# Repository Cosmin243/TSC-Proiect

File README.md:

# OpenBook – Cititor de Cărți Electronice Open-Source

OpenBook este un dispozitiv de tip e-book reader cu sursă deschisă, proiectat să fie accesibil și eficient. Creat în cadrul inițiativei TSC, dispozitivul este construit în jurul microcontrolerului ESP32-C6, oferind funcții avansate de afișare, conectivitate și consum energetic redus. Designul său este pregătit pentru producția de serie.

# Diagrama

# [BOM] - Bill of Materials

| Componentă             | Descriere                            | Link |
|------------------------|--------------------------------------|------|
| ESP32-C6-WROOM-1-N8    | Wi-Fi, BLE, Zigbee SoC Module        | [Link](https://www.snapeda.com/parts/ESP32-C6-WROOM-1-N8/Espressif+Systems/view-part/) |
| BME680                 | Environmental Sensor                 | [Link](https://www.snapeda.com/parts/BME680/Bosch/view-part/?welcome=home) |
| MCP73831               | Li-Po Battery Charging Controller    | [Link](https://www.digikey.com/en/products/detail/microchip-technology/MCP73831T-2ACI-OT/1874108) |
| DS3231SN               | Real-Time Clock                      | [Link](https://www.snapeda.com/parts/DS3231SN%23/Analog+Devices/view-part/) |
| MAX17048G+T10          | Battery Fuel Gauge                   | [Link](https://www.digikey.com/en/products/detail/analog-devices-inc-maxim-integrated/MAX17048G-T10/9357632) |
| W25Q512JVEIQ           | 512Mb Flash Memory                   | [Link](https://www.snapeda.com/parts/W25Q512JVEIQ/Winbond/view-part/) |
| USB4110-GF-A           | USB Type-C Connector                 | [Link](https://www.digikey.com/en/products/detail/amphenol-commercial-products/USB4110-GF-A/6039334) |
| 112A-TAAR-R03          | Micro SD Card Connector              | [Link](https://store.comet.bg/en/Catalogue/Product/43497/) |
| XC6220A331MR-G         | LDO Voltage Regulator                | [Link](https://www.lcsc.com/product-detail/LDO-Voltage-Regulators_Torex-Semicon-XC6220A331MR-G_C35154.html) |
| SI1308EDL-T1-GE3       | N-Channel MOSFET                     | [Link](https://www.digikey.com/en/products/detail/vishay-siliconix/SI1308EDL-T1-GE3/770967) |
| DMG2305UX-7            | P-Channel MOSFET                     | [Link](https://www.digikey.com/en/products/detail/diodes-incorporated/DMG2305UX-7/2713557) |
| USBLC6-2SC6Y           | USB ESD Protection                   | [Link](https://www.digikey.com/en/products/detail/stmicroelectronics/USBLC6-2SC6Y/458756) |
| MBR0530                | Schottky Diode                       | [Link](https://www.digikey.com/en/products/detail/onsemi/MBR0530T1G/965411) |
| CPH3225                | 11mF Supercapacitor                  | [Link](https://www.snapeda.com/parts/CPH3225A/Seiko+Instruments/view-part/) |
| CC0402                 | Capacitor                            | [Link](https://componentsearchengine.com/part-view/CC0402MRX5R5BB106/YAGEO) |
| RR0402                 | Resistor                             | [Link](https://www.snapeda.com/parts/RC0402FR-07226RL/Yageo/view-part/) |

Dispozitivul suportă mai multe surse de alimentare:

- **USB-C**: Alimentare și comunicare prin conectorul `USB4110-GF-A`, cu protecție ESD (`USBLC6-2SC6Y`)
- **Baterie Li-Po**: Încărcată prin controlerul `MCP73831`, cu indicator de stare LED
- **Backup cu supercondensator**: `CPH3225A` menține alimentarea ceasului RTC în caz de pierdere de curent

**Calea de alimentare include:**

- `XC6220A331MR-G` – LDO care furnizează 3.3V stabil pentru sistem
- `MAX17048G+T10` – Fuel gauge pentru monitorizarea capacității bateriei
- `DMG2305UX-7` – MOSFET P-Channel pentru selecția automată a sursei de alimentare
- `MBR0530` – Diodă Schottky pentru protecție la tensiuni inverse

---

## Procesare & Memorie

- `ESP32-C6-WROOM-1-N8` – Microcontroller principal cu suport pentru Wi-Fi 6, Bluetooth 5 și Zigbee 3.0
- `W25Q512JVEIQ` – Memorie Flash SPI externă de 512Mb pentru stocare extinsă
- **Slot microSD** – Permite extinderea stocării pentru datele utilizatorului

---

## Senzori & Ceas

- `BME680` – Senzor ambiental I²C ce măsoară:
  - Temperatură: -40°C până la +85°C  
  - Umiditate: 0–100% RH  
  - Presiune: 300–1100 hPa  
  - Calitatea aerului (rezistență la gaze)
- `DS3231SN` – Ceas în timp real I²C cu compensare termică, foarte precis

---

## Conectivitate & Interfețe

- **USB-C** – Pentru alimentare, încărcare și comunicare de date
- **Qwiic / STEMMA QT** – Conector I²C rapid pentru extensii externe (senzori, periferice)
- **I²C & SPI** – Utilizate pentru senzori și memorie
- **Mod Deep Sleep** – ESP32 intră în standby (~20 µA) pentru autonomie crescută

---

## Interfață Utilizator

- **Buton Reset** – Repornește dispozitivul
- **Buton Boot** – Permite accesul în modul bootloader pentru programare
- **Buton Change** – Poate fi folosit pentru interacțiuni cu conținutul afișat

# 🧷 Pini ESP32-C6

| GPIO  | Componentă       |
|-------|------------------|
| IO9   | Boot Button      |
| IO2   | SD Card          |
| IO4   | SD Card          |
| IO21  | I2C Shared       |
| IO6   | SPI Shared       |
| IO22  | I2C Shared       |
| IO7   | SPI Shared       |
| IO0   | RTC              |
| IO13  | USB Interface    |
| IO19  | MAX17048         |
| IO11  | NOR Flash        |
| IO12  | USB Interface    |
| IO1   | RTC              |
| IO8   | GPIO             |
| IO15  | Buton Change     |
| IO18  | RTC              |
| IO17  | UART             |
| IO16  | UART             |
| EN    | Buton Reset      |

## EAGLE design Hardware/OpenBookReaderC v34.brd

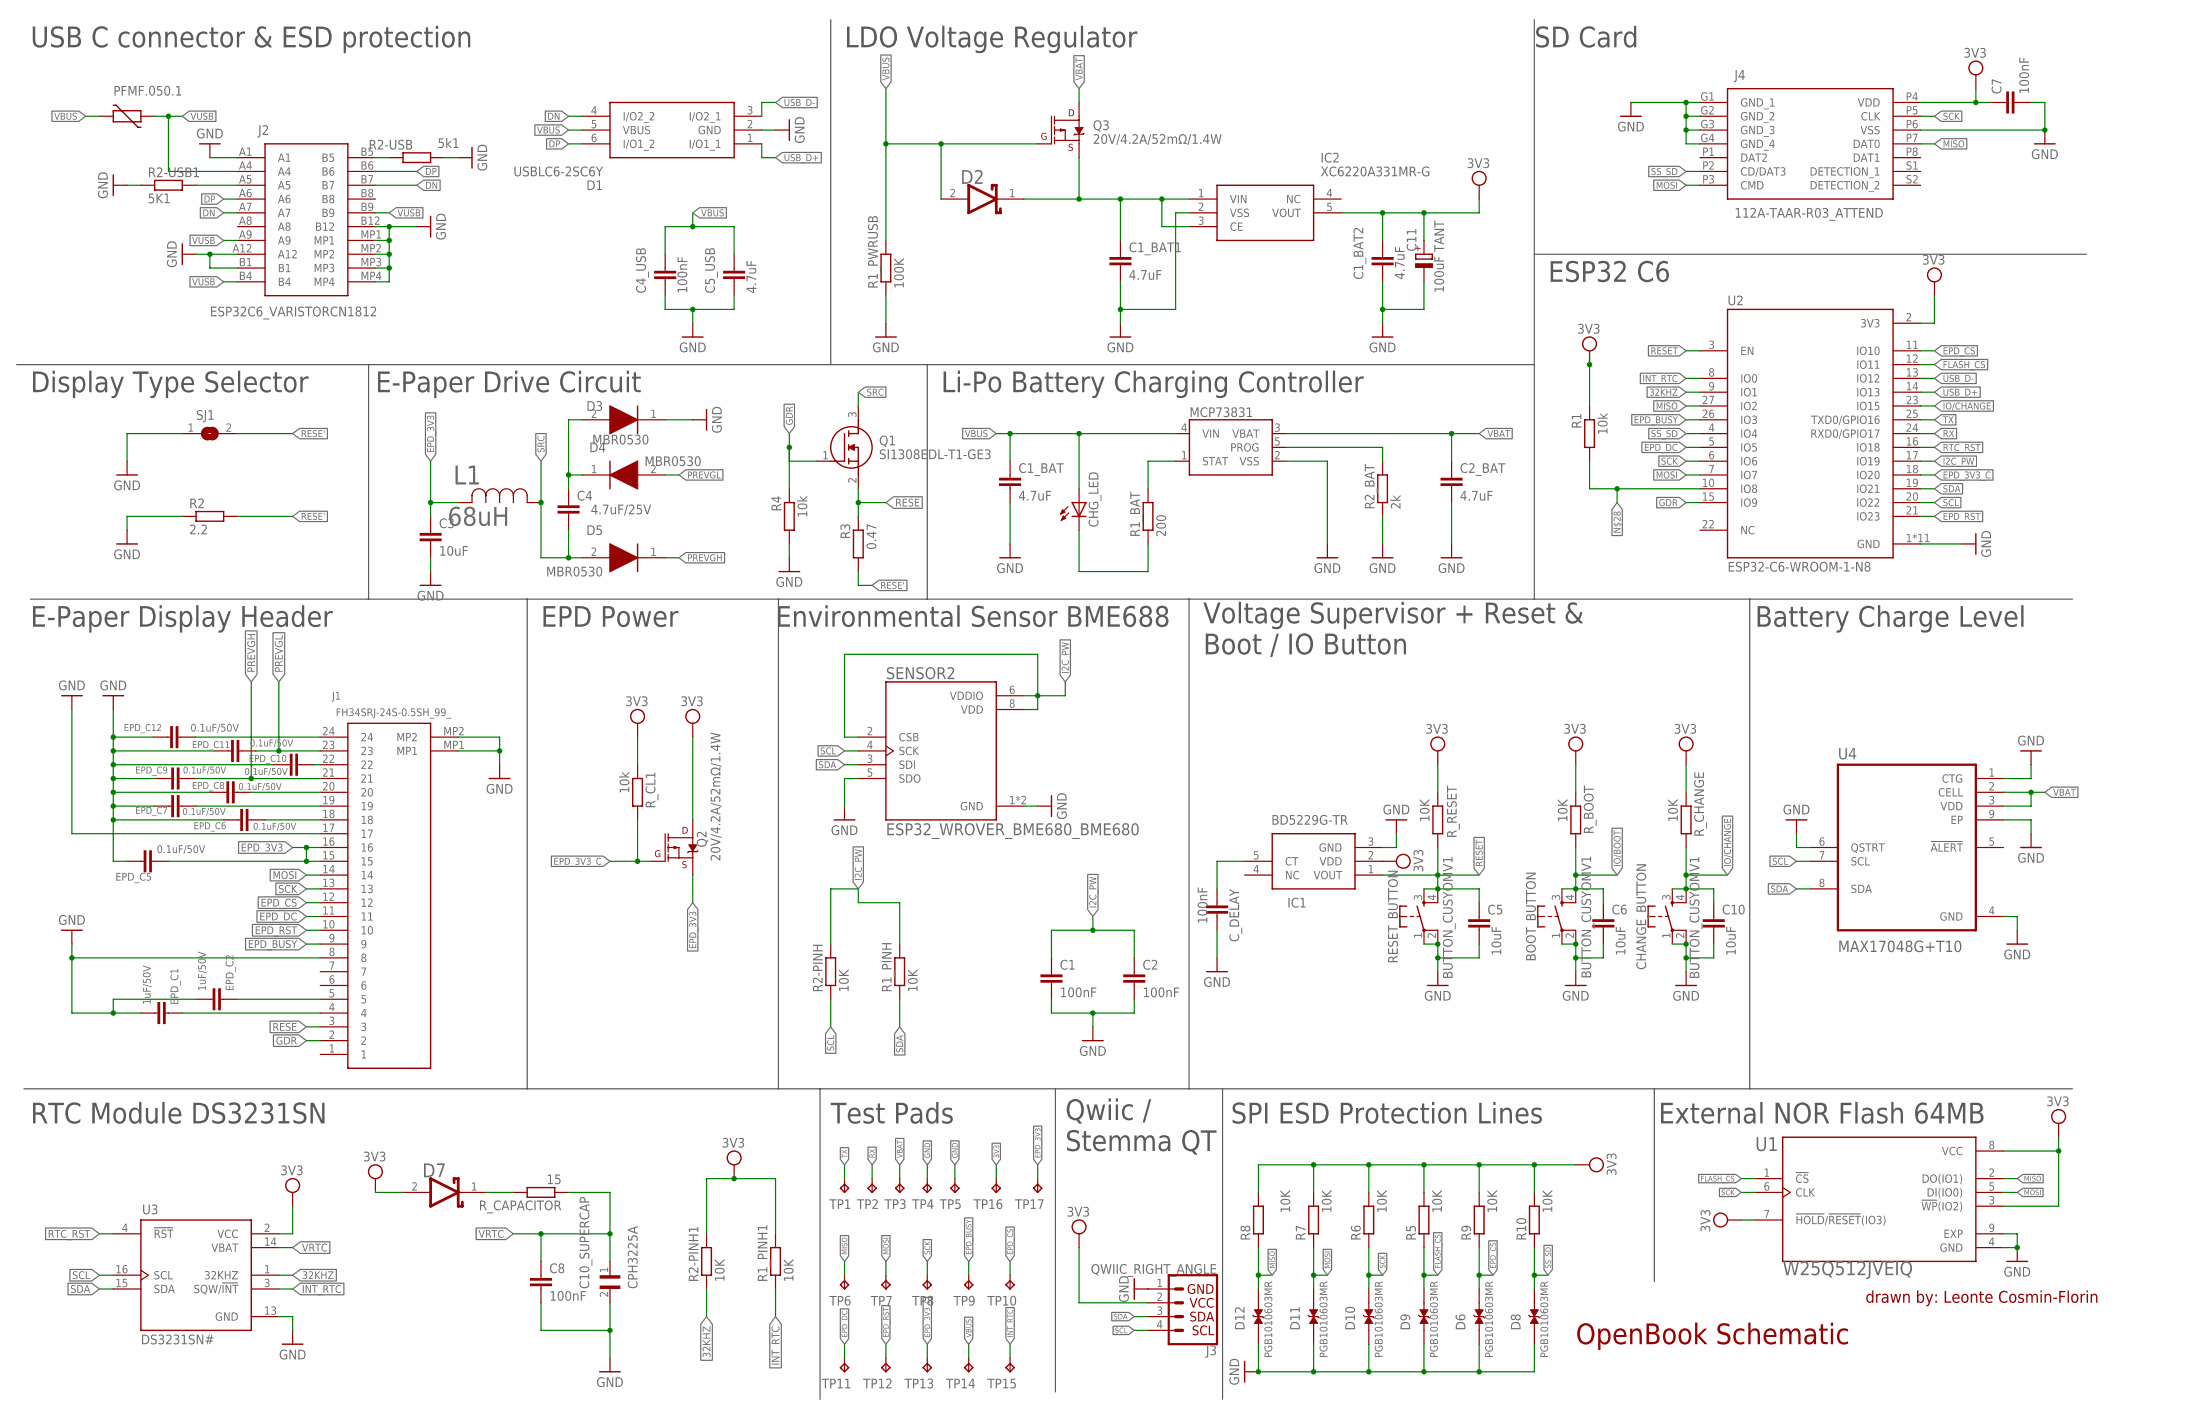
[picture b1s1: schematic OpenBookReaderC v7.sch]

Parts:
BOOT_BUTTON: BUTTON_CUSYOMV1; MYBUTTON
C1, C2, C4_USB, C7, C8: 100nF; ESP32_WROVER_EAGLE-LTSPICE_C0402
C1_BAT, C1_BAT1, C1_BAT2, C2_BAT, C5_USB: 4.7uF; ESP32_WROVER_EAGLE-LTSPICE_C0402
C3, C5, C6, C10: 10uF; ESP32_WROVER_EAGLE-LTSPICE_C0402
C4: 4.7uF/25V; ESP32_WROVER_EAGLE-LTSPICE_C0402
C10_SUPERCAP: CPH3225A; CAPCP3225X100N
C11: 100uF TANT; RCL_CT3528
CHANGE_BUTTON: BUTTON_CUSYOMV1; MYBUTTON
CHG_LED: ADAFRUIT_LEDCHIP-LED0603; ADAFRUIT_CHIP-LED0603
C_DELAY: 100nF; ESP32_WROVER_EAGLE-LTSPICE_C0402
D1: USBLC6-2SC6Y; SOT95P280X145-6N
D2, D7: ESP32_WROVER_AVX---SD0805S020S1R0_AVX_SD0805S020S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; ESP32_WROVER_AVX---SD0805S020S1R0_AVX_SD0805S020S1R0_0
D3, D4, D5: MBR0530; SOD3716X135N
D6, D8, D9, D10, D11, D12: PGB1010603MR; DIOC1608X36N
EPD_C1, EPD_C2: 1uF/50V; ESP32_WROVER_EAGLE-LTSPICE_C0402
EPD_C5, EPD_C6, EPD_C7, EPD_C8, EPD_C9, EPD_C10, EPD_C11, EPD_C12: 0.1uF/50V; ESP32_WROVER_EAGLE-LTSPICE_C0402
IC1: BD5229G-TR; SOT95P280X125-5N
IC2: XC6220A331MR-G; SOT95P280X120-5N
J1: FH34SRJ-24S-0.5SH_99_; FH34SRJ24S05SH99
J2: SAMACSYS_PARTS_USB4110-GF-A; SAMACSYS_PARTS_USB4110GFA
J3: QWIIC_RIGHT_ANGLE; JST04_1MM_RA
J4: 112A-TAAR-R03_ATTEND; 112ATAARR03ATTEND
L1: 68uH; IND_4828-WE-TPC_WRE
MCP73831: ESP32_WROVER_SPARKFUN-IC-POWER_MCP73831; ESP32_WROVER_SPARKFUN-IC-POWER_SOT23-5
PFMF.050.1: ESP32C6_VARISTORCN1812; ESP32C6_VARISTOR_CT/CN1812
Q1: SI1308EDL-T1-GE3; SOT65P210X110-3N
Q2, Q3: 20V/4.2A/52mΩ/1.4W; ESP32_WROVER_SPARKFUN-DISCRETESEMI_SOT23-3
R1, R4: 10k; ESP32_WROVER_EAGLE-LTSPICE_R0402
R1_BAT: 200; ESP32_WROVER_EAGLE-LTSPICE_R0402
R1_PINH, R1_PINH1, R2-PINH, R2-PINH1, R5, R6, R7, R8, R9, R10: 10K; ESP32_WROVER_EAGLE-LTSPICE_R0402
R1_PWRUSB: 100K; ESP32_WROVER_EAGLE-LTSPICE_R0402
R2: 2.2; ESP32_WROVER_EAGLE-LTSPICE_R0402
R2-USB: 5k1; ESP32_WROVER_EAGLE-LTSPICE_R0402
R2-USB1: 5K1; ESP32_WROVER_EAGLE-LTSPICE_R0402
R2_BAT: 2k; ESP32_WROVER_EAGLE-LTSPICE_R0402
R3: 0.47; ESP32_WROVER_EAGLE-LTSPICE_R0402
RESET_BUTTON: BUTTON_CUSYOMV1; MYBUTTON
R_BOOT: 10K; ESP32_WROVER_EAGLE-LTSPICE_R0402
R_CAPACITOR: 15; ESP32_WROVER_EAGLE-LTSPICE_R0402
R_CHANGE: 10K; ESP32_WROVER_EAGLE-LTSPICE_R0402
R_CL1: 10k; ESP32_WROVER_EAGLE-LTSPICE_R0402
R_RESET: 10K; ESP32_WROVER_EAGLE-LTSPICE_R0402
SENSOR2: ESP32_WROVER_BME680_BME680; ESP32_WROVER_BME680_PSON80P300X300X100-8N
SJ1: SJ
TP1, TP2, TP3, TP4, TP5, TP6, TP7, TP8, TP9, TP10, TP11, TP12, TP13, TP14, TP15, TP16, TP17: TPTP20R; TP20R
U1: W25Q512JVEIQ; SON127P600X800X80-9N
U2: ESP32-C6-WROOM-1-N8; XCVR_ESP32-C6-WROOM-1-N8
U3: DS3231SN#; SOIC127P1032X265-16N
U4: MAX17048G+T10; SON50P200X200X80-9N

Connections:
3V3: C1_BAT2.1, C7.1, C11.+, D7.2 (ANODE), IC1.2 (VDD), IC2.5 (VOUT), J3.2, J4.P4 (VDD), Q2.3 (D), R1.1, R1_PINH1.2, R2-PINH1.2, R5.2, R6.2, R7.2, R8.2, R9.2, R10.2, R_BOOT.1, R_CHANGE.1, R_CL1.1, R_RESET.1, TP16.TP, U1.3 (!WP!(IO2)), U1.7 (!HOLD!/!RESET!(IO3)), U1.8 (VCC), U2.2 (3V3), U3.2 (VCC)
32KHZ: R2-PINH1.1, U2.9 (IO1), U3.1 (32KHZ)
DN: D1.4 (I/O2_2), J2.A7, J2.B7
DP: D1.6 (I/O1_2), J2.A6, J2.B6
EPD_3V3: C3.1, EPD_C5.1, J1.15, J1.16, L1.2, Q2.2 (S), TP17.TP
EPD_3V3_C: Q2.1 (G), R_CL1.2, TP13.TP, U2.18 (IO20)
EPD_BUSY: J1.9, TP9.TP, U2.26 (IO3)
EPD_CS: D6.2, J1.12, R9.1, TP10.TP, U2.11 (IO10)
EPD_DC: J1.11, TP11.TP, U2.5 (IO5)
EPD_RST: J1.10, TP12.TP, U2.21 (IO23)
FLASH_CS: D9.2, R5.1, U1.1 (!CS), U2.12 (IO11)
GDR: J1.2, Q1.1 (G), R4.1, U2.15 (IO9)
GND: BOOT_BUTTON.1, BOOT_BUTTON.2, C1.2, C1_BAT.2, C1_BAT1.2, C1_BAT2.2, C2.2, C2_BAT.2, C3.2, C4_USB.2, C5.2, C5_USB.2, C6.2, C7.2, C8.2, C10.2, C10_SUPERCAP.2, C11.-, CHANGE_BUTTON.1, CHANGE_BUTTON.2, C_DELAY.2, D1.2 (GND), D3.1 (K), D6.1, D8.1, D9.1, D10.1, D11.1, D12.1, EPD_C1.2, EPD_C2.2, EPD_C5.2, EPD_C6.2, EPD_C7.2, EPD_C8.2, EPD_C9.2, EPD_C10.2, EPD_C11.2, EPD_C12.2, IC1.3 (GND), IC2.2 (VSS), J1.8, J1.17, J1.MP1, J1.MP2, J2.A1, J2.A12, J2.B1, J2.B12, J2.MP1, J2.MP2, J2.MP3, J2.MP4, J3.1, J4.G1 (GND_1), J4.G2 (GND_2), J4.G3 (GND_3), J4.G4 (GND_4), J4.P6 (VSS), MCP73831.2 (VSS), R1_PWRUSB.1, R2.1, R2-USB.2, R2-USB1.1, R2_BAT.1, R4.2, RESET_BUTTON.1, RESET_BUTTON.2, SENSOR2.1 (GND), SENSOR2.5 (SDO), SENSOR2.7 (GND), SJ1.1, TP4.TP, TP5.TP, U1.4 (GND), U1.9 (EXP), U2.1 (GND), U2.28 (GND), U2.29_1 (GND), U2.29_2 (GND), U2.29_3 (GND), U2.29_4 (GND), U2.29_5 (GND), U2.29_6 (GND), U2.29_7 (GND), U2.29_8 (GND), U2.29_9 (GND), U3.13 (GND), U4.1 (CTG), U4.4 (GND), U4.6 (QSTRT), U4.9 (EP)
I2C_PW: C1.1, C2.1, R1_PINH.2, R2-PINH.2, SENSOR2.2 (CSB), SENSOR2.6 (VDDIO), SENSOR2.8 (VDD), U2.17 (IO19)
INT_RTC: R1_PINH1.1, TP15.TP, U2.8 (IO0), U3.3 (SQW/!INT)
IO/BOOT: BOOT_BUTTON.3, BOOT_BUTTON.4, C6.1, R_BOOT.2
IO/CHANGE: C10.1, CHANGE_BUTTON.3, CHANGE_BUTTON.4, R_CHANGE.2, U2.23 (IO15)
MISO: D12.2, J4.P7 (DAT0), R8.1, TP6.TP, U1.2 (DO(IO1)), U2.27 (IO2)
MOSI: D11.2, J1.14, J4.P3 (CMD), R7.1, TP7.TP, U1.5 (DI(IO0)), U2.7 (IO7)
unnamed: EPD_C1.1, J1.4
unnamed: EPD_C2.1, J1.5
unnamed: D7.1 (CATHODE), R_CAPACITOR.2
unnamed: EPD_C6.1, J1.18
unnamed: EPD_C7.1, J1.19
unnamed: EPD_C8.1, J1.20
unnamed: C_DELAY.1, IC1.5 (CT)
unnamed: EPD_C10.1, J1.22
unnamed: C4.1, D3.2 (A), D4.1 (K)
unnamed: EPD_C12.1, J1.24
unnamed: J2.B5, R2-USB.1
unnamed: MCP73831.1 (STAT), R1_BAT.2
unnamed: CHG_LED.C, R1_BAT.1
unnamed: MCP73831.5 (PROG), R2_BAT.2
unnamed: C1_BAT1.1, D2.1 (CATHODE), IC2.1 (VIN), IC2.3 (CE), Q3.2 (S)
unnamed: J2.A5, R2-USB1.2
unnamed: R1.2, U2.10 (IO8)
PREVGH: D5.1 (K), EPD_C9.1, J1.21
PREVGL: D4.2 (A), EPD_C11.1, J1.23
RESE: J1.3, Q1.2 (S), R3.1
RESE': R2.2, R3.2, SJ1.2
RESET: C5.1, IC1.1 (VOUT), RESET_BUTTON.3, RESET_BUTTON.4, R_RESET.2, U2.3 (EN)
RTC_RST: U2.16 (IO18), U3.4 (!RST)
RX: TP2.TP, U2.24 (RXD0/GPIO17)
SCK: D10.2, J1.13, J4.P5 (CLK), R6.1, TP8.TP, U1.6 (CLK), U2.6 (IO6)
SCL: J3.4, R2-PINH.1, SENSOR2.4 (SCK), U2.20 (IO22), U3.16 (SCL), U4.7 (SCL)
SDA: J3.3, R1_PINH.1, SENSOR2.3 (SDI), U2.19 (IO21), U3.15 (SDA), U4.8 (SDA)
SRC: C4.2, D5.2 (A), L1.1, Q1.3 (D)
SS_SD: D8.2, J4.P2 (CD/DAT3), R10.1, U2.4 (IO4)
TX: TP1.TP, U2.25 (TXD0/GPIO16)
USB_D+: D1.1 (I/O1_1), U2.14 (IO13)
USB_D-: D1.3 (I/O2_1), U2.13 (IO12)
VBAT: C2_BAT.1, MCP73831.3 (VBAT), Q3.3 (D), TP3.TP, U4.2 (CELL), U4.3 (VDD)
VBUS: C1_BAT.1, C4_USB.1, C5_USB.1, CHG_LED.A, D1.5 (VBUS), D2.2 (ANODE), MCP73831.4 (VIN), PFMF.050.1.2, Q3.1 (G), R1_PWRUSB.2, TP14.TP
VRTC: C8.1, C10_SUPERCAP.1, R_CAPACITOR.1, U3.14 (VBAT)
VUSB: J2.A4, J2.A9, J2.B4, J2.B9, PFMF.050.1.1

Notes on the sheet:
E-Paper Display Header
RTC Module DS3231SN
Test Pads
Qwiic / Stemma QT
SPI ESD Protection Lines
External NOR Flash 64MB
Battery Charge Level
Voltage Supervisor + Reset & Boot / IO Button
Environmental Sensor BME688
EPD Power
Display Type Selector
E-Paper Drive Circuit
Li-Po Battery Charging Controller
ESP32 C6
SD Card
LDO Voltage Regulator
USB C connector & ESD protection
OpenBook Schematic
drawn by: Leonte Cosmin-Florin

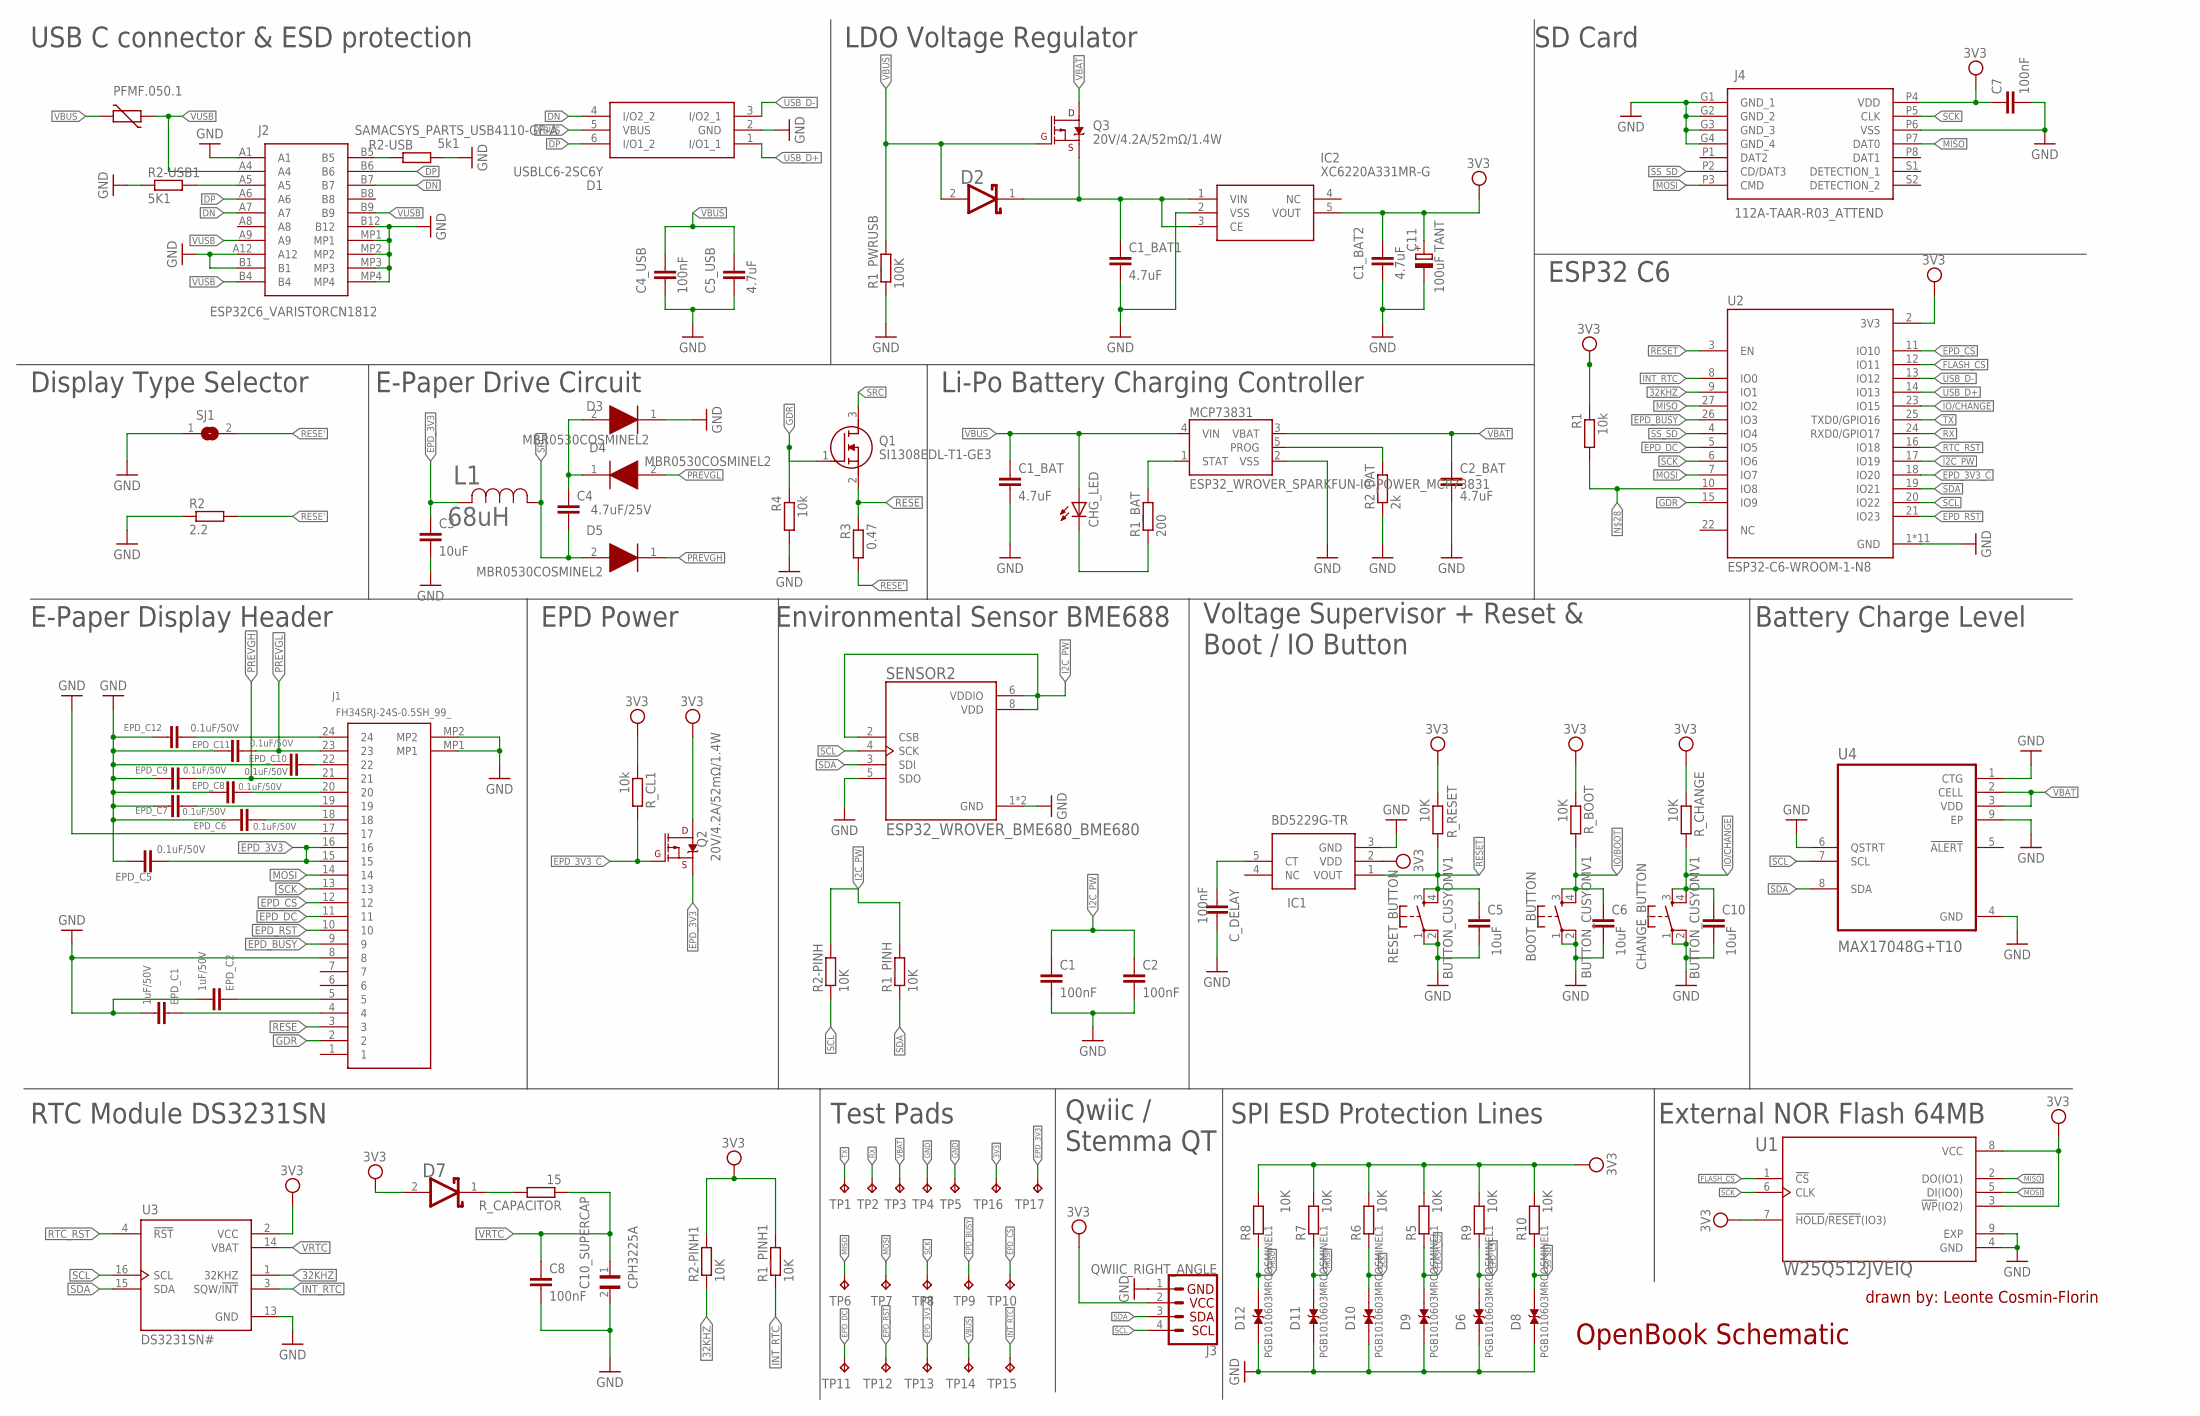
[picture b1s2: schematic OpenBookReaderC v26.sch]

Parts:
BOOT_BUTTON: BUTTON_CUSYOMV1; MYBUTTON
C1, C2, C4_USB, C7, C8: 100nF; ESP32_WROVER_EAGLE-LTSPICE_C0402
C1_BAT, C1_BAT1, C1_BAT2, C2_BAT, C5_USB: 4.7uF; ESP32_WROVER_EAGLE-LTSPICE_C0402
C3, C5, C6, C10: 10uF; ESP32_WROVER_EAGLE-LTSPICE_C0402
C4: 4.7uF/25V; ESP32_WROVER_EAGLE-LTSPICE_C0402
C10_SUPERCAP: CPH3225A; CAPCP3225X100N
C11: 100uF TANT; RCL_CT3528
CHANGE_BUTTON: BUTTON_CUSYOMV1; MYBUTTON
CHG_LED: ADAFRUIT_LEDCHIP-LED0603; ADAFRUIT_CHIP-LED0603
C_DELAY: 100nF; ESP32_WROVER_EAGLE-LTSPICE_C0402
D1: USBLC6-2SC6Y; SOT95P280X145-6N
D2, D7: ESP32_WROVER_AVX---SD0805S020S1R0_AVX_SD0805S020S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; ESP32_WROVER_AVX---SD0805S020S1R0_AVX_SD0805S020S1R0_0
D3, D4, D5: MBR0530COSMINEL2; SOD3716X135N
D6, D8, D9, D10, D11, D12: PGB1010603MRCOSMINEL1; DIOC1608X36N
EPD_C1, EPD_C2: 1uF/50V; ESP32_WROVER_EAGLE-LTSPICE_C0402
EPD_C5, EPD_C6, EPD_C7, EPD_C8, EPD_C9, EPD_C10, EPD_C11, EPD_C12: 0.1uF/50V; ESP32_WROVER_EAGLE-LTSPICE_C0402
IC1: BD5229G-TR; SOT95P280X125-5N
IC2: XC6220A331MR-G; SOT95P280X120-5N
J1: FH34SRJ-24S-0.5SH_99_; FH34SRJ24S05SH99
J2: SAMACSYS_PARTS_USB4110-GF-A; SAMACSYS_PARTS_USB4110GFA
J3: QWIIC_RIGHT_ANGLE; JST04_1MM_RA
J4: 112A-TAAR-R03_ATTEND; 112ATAARR03ATTEND
L1: 68uH; IND_4828-WE-TPC_WRE
MCP73831: ESP32_WROVER_SPARKFUN-IC-POWER_MCP73831; ESP32_WROVER_SPARKFUN-IC-POWER_SOT23-5
PFMF.050.1: ESP32C6_VARISTORCN1812; ESP32C6_VARISTOR_CT/CN1812
Q1: SI1308EDL-T1-GE3; SOT65P210X110-3N
Q2, Q3: 20V/4.2A/52mΩ/1.4W; ESP32_WROVER_SPARKFUN-DISCRETESEMI_SOT23-3
R1, R4: 10k; ESP32_WROVER_EAGLE-LTSPICE_R0402
R1_BAT: 200; ESP32_WROVER_EAGLE-LTSPICE_R0402
R1_PINH, R1_PINH1, R2-PINH, R2-PINH1, R5, R6, R7, R8, R9, R10: 10K; ESP32_WROVER_EAGLE-LTSPICE_R0402
R1_PWRUSB: 100K; ESP32_WROVER_EAGLE-LTSPICE_R0402
R2: 2.2; ESP32_WROVER_EAGLE-LTSPICE_R0402
R2-USB: 5k1; ESP32_WROVER_EAGLE-LTSPICE_R0402
R2-USB1: 5K1; ESP32_WROVER_EAGLE-LTSPICE_R0402
R2_BAT: 2k; ESP32_WROVER_EAGLE-LTSPICE_R0402
R3: 0.47; ESP32_WROVER_EAGLE-LTSPICE_R0402
RESET_BUTTON: BUTTON_CUSYOMV1; MYBUTTON
R_BOOT: 10K; ESP32_WROVER_EAGLE-LTSPICE_R0402
R_CAPACITOR: 15; ESP32_WROVER_EAGLE-LTSPICE_R0402
R_CHANGE: 10K; ESP32_WROVER_EAGLE-LTSPICE_R0402
R_CL1: 10k; ESP32_WROVER_EAGLE-LTSPICE_R0402
R_RESET: 10K; ESP32_WROVER_EAGLE-LTSPICE_R0402
SENSOR2: ESP32_WROVER_BME680_BME680; ESP32_WROVER_BME680_PSON80P300X300X100-8N
SJ1: SJ
TP1, TP2, TP3, TP4, TP5, TP6, TP7, TP8, TP9, TP10, TP11, TP12, TP13, TP14, TP15, TP16, TP17: TP; TP20R
U1: W25Q512JVEIQ; SON127P600X800X80-9N
U2: ESP32-C6-WROOM-1-N8; XCVR_ESP32-C6-WROOM-1-N8
U3: DS3231SN#; SOIC127P1032X265-16N
U4: MAX17048G+T10; SON50P200X200X80-9N

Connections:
3V3: C1_BAT2.1, C7.1, C11.+, D7.2 (ANODE), IC1.2 (VDD), IC2.5 (VOUT), J3.2, J4.P4 (VDD), Q2.3 (D), R1.1, R1_PINH1.2, R2-PINH1.2, R5.2, R6.2, R7.2, R8.2, R9.2, R10.2, R_BOOT.1, R_CHANGE.1, R_CL1.1, R_RESET.1, TP16.TP, U1.3 (!WP!(IO2)), U1.7 (!HOLD!/!RESET!(IO3)), U1.8 (VCC), U2.2 (3V3), U3.2 (VCC)
32KHZ: R2-PINH1.1, U2.9 (IO1), U3.1 (32KHZ)
DN: D1.4 (I/O2_2), J2.A7, J2.B7
DP: D1.6 (I/O1_2), J2.A6, J2.B6
EPD_3V3: C3.1, EPD_C5.1, J1.15, J1.16, L1.2, Q2.2 (S), TP17.TP
EPD_3V3_C: Q2.1 (G), R_CL1.2, TP13.TP, U2.18 (IO20)
EPD_BUSY: J1.9, TP9.TP, U2.26 (IO3)
EPD_CS: D6.2, J1.12, R9.1, TP10.TP, U2.11 (IO10)
EPD_DC: J1.11, TP11.TP, U2.5 (IO5)
EPD_RST: J1.10, TP12.TP, U2.21 (IO23)
FLASH_CS: D9.2, R5.1, U1.1 (!CS), U2.12 (IO11)
GDR: J1.2, Q1.1 (G), R4.1, U2.15 (IO9)
GND: BOOT_BUTTON.1, BOOT_BUTTON.2, C1.2, C1_BAT.2, C1_BAT1.2, C1_BAT2.2, C2.2, C2_BAT.2, C3.2, C4_USB.2, C5.2, C5_USB.2, C6.2, C7.2, C8.2, C10.2, C10_SUPERCAP.2, C11.-, CHANGE_BUTTON.1, CHANGE_BUTTON.2, C_DELAY.2, D1.2 (GND), D3.1 (K), D6.1, D8.1, D9.1, D10.1, D11.1, D12.1, EPD_C1.2, EPD_C2.2, EPD_C5.2, EPD_C6.2, EPD_C7.2, EPD_C8.2, EPD_C9.2, EPD_C10.2, EPD_C11.2, EPD_C12.2, IC1.3 (GND), IC2.2 (VSS), J1.8, J1.17, J1.MP1, J1.MP2, J2.A1, J2.A12, J2.B1, J2.B12, J2.MP1, J2.MP2, J2.MP3, J2.MP4, J3.1, J4.G1 (GND_1), J4.G2 (GND_2), J4.G3 (GND_3), J4.G4 (GND_4), J4.P6 (VSS), MCP73831.2 (VSS), R1_PWRUSB.1, R2.1, R2-USB.2, R2-USB1.1, R2_BAT.1, R4.2, RESET_BUTTON.1, RESET_BUTTON.2, SENSOR2.1 (GND), SENSOR2.5 (SDO), SENSOR2.7 (GND), SJ1.1, TP4.TP, TP5.TP, U1.4 (GND), U1.9 (EXP), U2.1 (GND), U2.28 (GND), U2.29_1 (GND), U2.29_2 (GND), U2.29_3 (GND), U2.29_4 (GND), U2.29_5 (GND), U2.29_6 (GND), U2.29_7 (GND), U2.29_8 (GND), U2.29_9 (GND), U3.13 (GND), U4.1 (CTG), U4.4 (GND), U4.6 (QSTRT), U4.9 (EP)
I2C_PW: C1.1, C2.1, R1_PINH.2, R2-PINH.2, SENSOR2.2 (CSB), SENSOR2.6 (VDDIO), SENSOR2.8 (VDD), U2.17 (IO19)
INT_RTC: R1_PINH1.1, TP15.TP, U2.8 (IO0), U3.3 (SQW/!INT)
IO/BOOT: BOOT_BUTTON.3, BOOT_BUTTON.4, C6.1, R_BOOT.2
IO/CHANGE: C10.1, CHANGE_BUTTON.3, CHANGE_BUTTON.4, R_CHANGE.2, U2.23 (IO15)
MISO: D12.2, J4.P7 (DAT0), R8.1, TP6.TP, U1.2 (DO(IO1)), U2.27 (IO2)
MOSI: D11.2, J1.14, J4.P3 (CMD), R7.1, TP7.TP, U1.5 (DI(IO0)), U2.7 (IO7)
unnamed: EPD_C1.1, J1.4
unnamed: EPD_C2.1, J1.5
unnamed: D7.1 (CATHODE), R_CAPACITOR.2
unnamed: EPD_C6.1, J1.18
unnamed: EPD_C7.1, J1.19
unnamed: EPD_C8.1, J1.20
unnamed: C_DELAY.1, IC1.5 (CT)
unnamed: EPD_C10.1, J1.22
unnamed: C4.1, D3.2 (A), D4.1 (K)
unnamed: EPD_C12.1, J1.24
unnamed: J2.B5, R2-USB.1
unnamed: MCP73831.1 (STAT), R1_BAT.2
unnamed: CHG_LED.C, R1_BAT.1
unnamed: MCP73831.5 (PROG), R2_BAT.2
unnamed: C1_BAT1.1, D2.1 (CATHODE), IC2.1 (VIN), IC2.3 (CE), Q3.2 (S)
unnamed: J2.A5, R2-USB1.2
unnamed: R1.2, U2.10 (IO8)
PREVGH: D5.1 (K), EPD_C9.1, J1.21
PREVGL: D4.2 (A), EPD_C11.1, J1.23
RESE: J1.3, Q1.2 (S), R3.1
RESE': R2.2, R3.2, SJ1.2
RESET: C5.1, IC1.1 (VOUT), RESET_BUTTON.3, RESET_BUTTON.4, R_RESET.2, U2.3 (EN)
RTC_RST: U2.16 (IO18), U3.4 (!RST)
RX: TP2.TP, U2.24 (RXD0/GPIO17)
SCK: D10.2, J1.13, J4.P5 (CLK), R6.1, TP8.TP, U1.6 (CLK), U2.6 (IO6)
SCL: J3.4, R2-PINH.1, SENSOR2.4 (SCK), U2.20 (IO22), U3.16 (SCL), U4.7 (SCL)
SDA: J3.3, R1_PINH.1, SENSOR2.3 (SDI), U2.19 (IO21), U3.15 (SDA), U4.8 (SDA)
SRC: C4.2, D5.2 (A), L1.1, Q1.3 (D)
SS_SD: D8.2, J4.P2 (CD/DAT3), R10.1, U2.4 (IO4)
TX: TP1.TP, U2.25 (TXD0/GPIO16)
USB_D+: D1.1 (I/O1_1), U2.14 (IO13)
USB_D-: D1.3 (I/O2_1), U2.13 (IO12)
VBAT: C2_BAT.1, MCP73831.3 (VBAT), Q3.3 (D), TP3.TP, U4.2 (CELL), U4.3 (VDD)
VBUS: C1_BAT.1, C4_USB.1, C5_USB.1, CHG_LED.A, D1.5 (VBUS), D2.2 (ANODE), MCP73831.4 (VIN), PFMF.050.1.2, Q3.1 (G), R1_PWRUSB.2, TP14.TP
VRTC: C8.1, C10_SUPERCAP.1, R_CAPACITOR.1, U3.14 (VBAT)
VUSB: J2.A4, J2.A9, J2.B4, J2.B9, PFMF.050.1.1

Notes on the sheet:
E-Paper Display Header
RTC Module DS3231SN
Test Pads
Qwiic / Stemma QT
SPI ESD Protection Lines
External NOR Flash 64MB
Battery Charge Level
Voltage Supervisor + Reset & Boot / IO Button
Environmental Sensor BME688
EPD Power
Display Type Selector
E-Paper Drive Circuit
Li-Po Battery Charging Controller
ESP32 C6
SD Card
LDO Voltage Regulator
USB C connector & ESD protection
OpenBook Schematic
drawn by: Leonte Cosmin-Florin

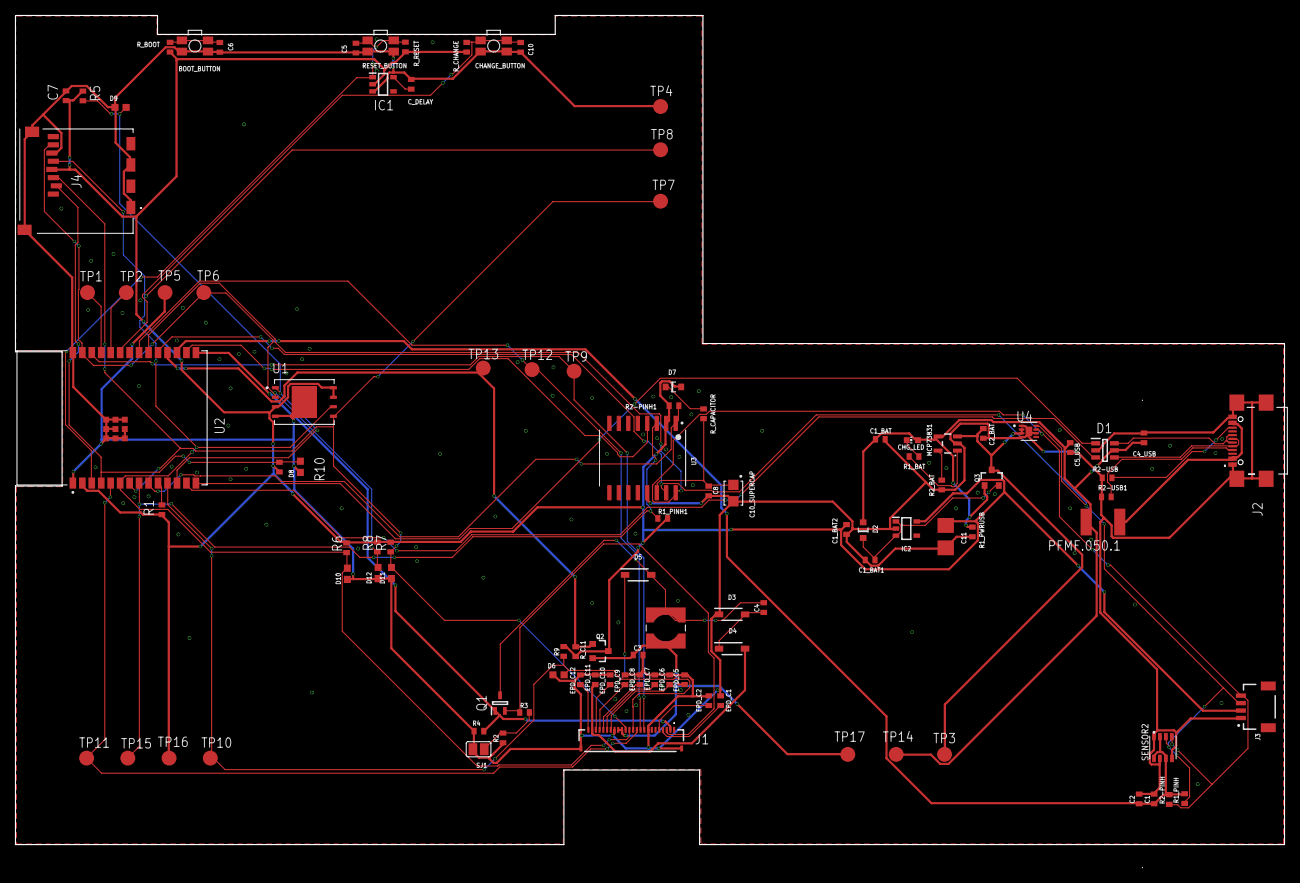
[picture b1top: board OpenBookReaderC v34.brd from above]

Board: 2 copper layers, 170.2 x 114.3 mm, 103 parts (0 on the bottom side), 55 nets.

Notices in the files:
parts and their libraries:
DeskAssistant v19 v1: COPYRIGHT: Copyright (C) 2024 Ultra Librarian. All rights reserved.
